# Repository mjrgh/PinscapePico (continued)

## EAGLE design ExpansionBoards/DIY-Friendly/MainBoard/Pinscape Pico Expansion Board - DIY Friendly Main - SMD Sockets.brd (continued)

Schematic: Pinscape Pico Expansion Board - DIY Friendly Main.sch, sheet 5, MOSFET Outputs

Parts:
C1, C3, C5, C7, C11, C13: 100nF; C025-024X044; PARTNO 21RZ310-RC
C2, C4, C6, C8, C12, C14: 4.7uF; C025-024X044; PARTNO 810-FG14X5R1H475KRT0
IC1, IC2, IC3, IC4, IC5, IC6: UCC27524P; DIP794W53P254L959H508Q8N
J3: 640445-5; HDRV5W117P0X396_1X5_1981X762X1
J4: 640445-9; SHDR9W117P0X396_1X9_3566X762X1
Q1, Q2, Q3, Q4, Q5, Q6, Q7, Q8, Q9, Q10, Q11, Q12: FDPF085N10A; TO220BV; PARTNO FDPF085N10A
R1, R2, R3, R4, R5, R6, R7, R8, R14, R15, R16, R17: 4R7; 0204/5; PARTNO 660-MFS1/4DCT52R47R0

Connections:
12V: C1.2, C2.2, C3.2, C4.2, C5.2, C6.2, C7.2, C8.2, C11.2, C12.2, C13.2, C14.2, IC1.1 (ENA), IC1.6 (VDD), IC1.8 (ENB), IC2.1 (ENA), IC2.6 (VDD), IC2.8 (ENB), IC3.1 (ENA), IC3.6 (VDD), IC3.8 (ENB), IC4.1 (ENA), IC4.6 (VDD), IC4.8 (ENB), IC5.1 (ENA), IC5.6 (VDD), IC5.8 (ENB), IC6.1 (ENA), IC6.6 (VDD), IC6.8 (ENB); also elsewhere on the board
unnamed: IC1.7 (OUTA), R1.1
unnamed: IC1.5 (OUTB), R2.1
unnamed: Q1.1 (G), R1.2
unnamed: Q2.1 (G), R2.2
unnamed: IC2.7 (OUTA), R3.1
unnamed: IC2.5 (OUTB), R4.1
unnamed: Q3.1 (G), R3.2
unnamed: Q4.1 (G), R4.2
unnamed: IC3.7 (OUTA), R5.1
unnamed: IC3.5 (OUTB), R6.1
unnamed: Q5.1 (G), R5.2
unnamed: Q6.1 (G), R6.2
unnamed: IC4.7 (OUTA), R7.1
unnamed: IC4.5 (OUTB), R8.1
unnamed: Q7.1 (G), R7.2
unnamed: Q8.1 (G), R8.2
unnamed: IC5.7 (OUTA), R14.1
unnamed: IC5.5 (OUTB), R15.1
unnamed: Q9.1 (G), R14.2
unnamed: Q10.1 (G), R15.2
unnamed: IC6.7 (OUTA), R16.1
unnamed: IC6.5 (OUTB), R17.1
unnamed: Q11.1 (G), R16.2
unnamed: Q12.1 (G), R17.2
OUT1: J4.1, Q1.2 (D)
OUT2: J4.3, Q2.2 (D)
OUT3: J4.4, Q3.2 (D)
OUT4: J4.5, Q4.2 (D)
OUT5: J4.6, Q5.2 (D)
OUT6: J4.7, Q6.2 (D)
OUT7: J4.8, Q7.2 (D)
OUT8: J4.9, Q8.2 (D)
OUT9: J3.1, Q9.2 (D)
OUT10: J3.3, Q10.2 (D)
OUT11: J3.4, Q11.2 (D)
OUT12: J3.5, Q12.2 (D)
OUTCTL1: IC1.2 (INA); also elsewhere on the board
OUTCTL2: IC1.4 (INB); also elsewhere on the board
OUTCTL3: IC2.2 (INA); also elsewhere on the board
OUTCTL4: IC2.4 (INB); also elsewhere on the board
OUTCTL5: IC3.2 (INA); also elsewhere on the board
OUTCTL6: IC3.4 (INB); also elsewhere on the board
OUTCTL7: IC4.2 (INA); also elsewhere on the board
OUTCTL8: IC4.4 (INB); also elsewhere on the board
OUTCTL9: IC5.2 (INA); also elsewhere on the board
OUTCTL10: IC5.4 (INB); also elsewhere on the board
OUTCTL11: IC6.2 (INA); also elsewhere on the board
OUTCTL12: IC6.4 (INB); also elsewhere on the board

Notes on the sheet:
High-power MOSFET drive ports
KEY
High-power MOSFET drivers

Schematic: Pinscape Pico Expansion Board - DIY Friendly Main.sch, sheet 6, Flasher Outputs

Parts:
IC7, IC8, IC9, IC10: ULN2803A; DIL18
J1: 30316-6002HB; 3M-30316-6002HB
J13: 640445-2; SHDR2W117P0X396_1X2_792X762X11

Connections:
5V: J1.2; also elsewhere on the board
FLASHCTL1: IC7.1 (I1), IC7.2 (I2); also elsewhere on the board
FLASHCTL2: IC7.3 (I3), IC7.4 (I4); also elsewhere on the board
FLASHCTL3: IC7.5 (I5), IC7.6 (I6); also elsewhere on the board
FLASHCTL4: IC7.7 (I7), IC7.8 (I8); also elsewhere on the board
FLASHCTL5: IC8.1 (I1), IC8.2 (I2); also elsewhere on the board
FLASHCTL6: IC8.3 (I3), IC8.4 (I4); also elsewhere on the board
FLASHCTL7: IC8.5 (I5), IC8.6 (I6); also elsewhere on the board
FLASHCTL8: IC8.7 (I7), IC8.8 (I8); also elsewhere on the board
FLASHCTL9: IC10.7 (I7), IC10.8 (I8); also elsewhere on the board
FLASHCTL10: IC10.5 (I5), IC10.6 (I6); also elsewhere on the board
FLASHCTL11: IC10.3 (I3), IC10.4 (I4); also elsewhere on the board
FLASHCTL12: IC10.1 (I1), IC10.2 (I2); also elsewhere on the board
FLASHCTL13: IC9.5 (I5), IC9.6 (I6); also elsewhere on the board
FLASHCTL14: IC9.3 (I3), IC9.4 (I4); also elsewhere on the board
FLASHCTL15: IC9.1 (I1), IC9.2 (I2); also elsewhere on the board
FLASHCTL16: IC9.7 (I7), IC9.8 (I8); also elsewhere on the board
FLASHER1: IC7.17 (O2), IC7.18 (O1), J1.15
FLASHER2: IC7.15 (O4), IC7.16 (O3), J1.13
FLASHER3: IC7.13 (O6), IC7.14 (O5), J1.11
FLASHER4: IC7.11 (O8), IC7.12 (O7), J1.9
FLASHER5: IC8.17 (O2), IC8.18 (O1), J1.7
FLASHER6: IC8.15 (O4), IC8.16 (O3), J1.5
FLASHER7: IC8.13 (O6), IC8.14 (O5), J1.3
FLASHER8: IC8.11 (O8), IC8.12 (O7), J1.1
FLASHER9: IC10.11 (O8), IC10.12 (O7), J1.16
FLASHER10: IC10.13 (O6), IC10.14 (O5), J1.14
FLASHER11: IC10.15 (O4), IC10.16 (O3), J1.12
FLASHER12: IC10.17 (O2), IC10.18 (O1), J1.10
FLASHER13: IC9.13 (O6), IC9.14 (O5), J1.8
FLASHER14: IC9.15 (O4), IC9.16 (O3), J1.6
FLASHER15: IC9.17 (O2), IC9.18 (O1), J1.4
FLASHER16: IC9.11 (O8), IC9.12 (O7), J13.1

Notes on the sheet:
RGB Flashers, 1A each port (designed 5x RGB) Pinscape v1 board compatible connector

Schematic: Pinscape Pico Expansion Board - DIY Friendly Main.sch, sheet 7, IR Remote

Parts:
C16: 4.7uF; C025-024X044; PARTNO 810-FG14X5R1H475KRT0
D3, D4: 1N4148; DO35-7
J10: 215079-4; 2150794
J11: 640454-2; HDRV2W66P0X254_1X2_762X572X100
Q13: BC337-25; BC33725
R19: 1.8K; 0204/7; PARTNO 660-MFS1/4DCT52R47R0
R31: 2R5; 0204/7; PARTNO 660-MFS1/4DCT52R47R0

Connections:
3V3_PICO: J10.1; also elsewhere on the board
5V: C16.1, J11.1; also elsewhere on the board
$N377: D3.A, Q13.2 (B), R19.2
IR_IN: J10.3; also elsewhere on the board
IR_LED_CATHODE: J11.2, Q13.1 (C)
IR_OUT: R19.1; also elsewhere on the board
unnamed: D3.C, D4.A
unnamed: Q13.3 (E), R31.2

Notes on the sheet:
IR REMOTE CONTROL TRANSMITTER Use with TSAL6400 IRED or equivalent, with a peak wavelength around 940nm. Set the current-sense resistor according to the desired forward current on the IR LED. The IR LED should be connected directly to the header (no external resistor is needed). Two IR LEDs can be 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
IR REMOTE RECEIVER CONNECTOR This header allows connecting an IR receiver (TSOP38438) on a separate circuit board, connected to the main board with a 4-conductor ribbon cable. The board should include the VCC supply filter circuit (220R + 150nF) shown in the data sheet.
===> IRED Cathode (-)
===> IRED Anode (+)
Note: TE Connectivity Micro-Match 215079-4 base pairs with 215083-4 on-cable IDC connector.
Resistor sets current to I(LED) = 0.5V/R R=2.5 ohms -> 200mA current
NPN substitutes: choose any medium-power NPN with Hfe around 100
IR EMITTER / IR RECEIVER The emitter and receiver are designed to be installed remotely to allow placing them in suitable line-of-sight locations.

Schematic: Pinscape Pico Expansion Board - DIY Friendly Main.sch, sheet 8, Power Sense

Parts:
C15: 100nF; C025-024X044; PARTNO 21RZ310-RC
IC13: SN74HC74NE4; DIP794W53P254L1930H508Q14N
IC14: PC827; DIL08
IC15: S-80833CLY; TO-92_(TO-226)
R18: 240R; 0204/7; PARTNO 660-MFS1/4DCT52R47R0
R20, R22: 10K; 0204/7; PARTNO 660-MFS1/4DCT52R47R0
R21: 360R; 0204/7; PARTNO 660-MFS1/4DCT52R47R0

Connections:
3V3_PICO: IC14.6 (COL); also elsewhere on the board
5V: C15.1, IC13.2 (1D), IC13.4 (1!PRE), IC13.14 (VCC), IC14.8 (COL), IC15.2 (VDD); also elsewhere on the board
unnamed: IC13.3 (1CLK), IC14.7 (EMIT), R20.1
unnamed: IC14.2 (C), R18.2
unnamed: IC13.1 (!1CLR), IC15.1 (OUT)
unnamed: IC14.4 (C), R21.2
unnamed: IC13.5 (1Q), IC14.3 (A)
PSU2_STATUS_SENSE: IC14.5 (EMIT), R22.2; also elsewhere on the board
PSU2_STATUS_SET: IC14.1 (A); also elsewhere on the board

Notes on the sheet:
PSU2 Power Sensing This circuit monitors the status of a secondary power supply (PSU2) that's hard-switched on and off with the overall pinball cabinet power. The status circuit maintains its own memory of the power state, independently of the Pico's power state, which satisfies two important condi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
POR part selection: The POR is triggered by the voltage on the 5V supply crossing a threshold voltage, so we must choose a POR whose threshold voltage slightly below the MINIMUM voltage that the 5V supply maintains when powered on and operating stably. Nominally, this would be 4.75V for an ATX supp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
Note: RESET signal must be ACTIVE LOW

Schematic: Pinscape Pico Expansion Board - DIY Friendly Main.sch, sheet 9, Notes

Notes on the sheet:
I2C Address Map (7-bit notation) $18 LIS3DH (Accelerometer) $30 Pico PWM Helper (main board) $31 Pico PWM Helper #1 (power board) $32 Pico PWM Helper #2 (power board) $48 ADS1115 (ADC) $68 DS1307 (RTC clock/calendar chip) [On Power board]

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
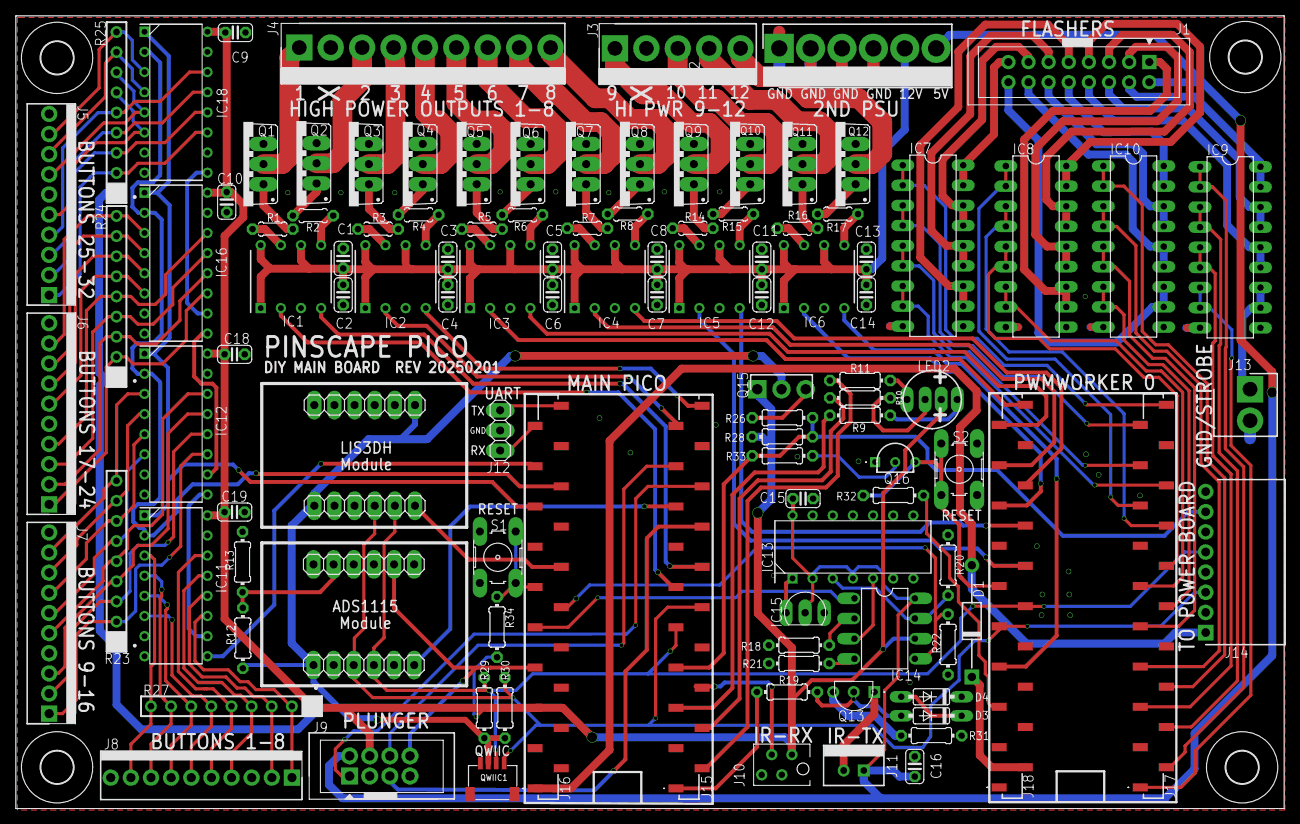
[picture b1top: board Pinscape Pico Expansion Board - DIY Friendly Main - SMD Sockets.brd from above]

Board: 2 copper layers, 160.0 x 100.0 mm, 117 parts (0 on the bottom side), 161 nets.

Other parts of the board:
J15, J16, J17, J18: M20-7862042B; M20-7862042-B
U$1, U$2, U$3, U$4: 4,1

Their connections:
3V3_PICO: J16.5; also elsewhere on the board
ACCEL_INTR: J16.12; also elsewhere on the board
ADC_INTR: J15.15; also elsewhere on the board
BUTTON_CLK: J16.16; also elsewhere on the board
BUTTON_DATA: J16.17; also elsewhere on the board
BUTTON_SHLD: J16.15; also elsewhere on the board
FLASHCTL1: J17.20; also elsewhere on the board
FLASHCTL2: J17.19; also elsewhere on the board
FLASHCTL3: J17.17; also elsewhere on the board
FLASHCTL4: J17.16; also elsewhere on the board
FLASHCTL5: J17.15; also elsewhere on the board
FLASHCTL6: J17.14; also elsewhere on the board
FLASHCTL7: J17.12; also elsewhere on the board
FLASHCTL8: J17.11; also elsewhere on the board
FLASHCTL9: J17.10; also elsewhere on the board
FLASHCTL10: J17.9; also elsewhere on the board
FLASHCTL11: J17.7; also elsewhere on the board
FLASHCTL12: J17.6; also elsewhere on the board
FLASHCTL13: J17.5; also elsewhere on the board
FLASHCTL14: J17.4; also elsewhere on the board
FLASHCTL15: J17.2; also elsewhere on the board
FLASHCTL16: J17.1; also elsewhere on the board
IR_IN: J15.6; also elsewhere on the board
IR_OUT: J15.1; also elsewhere on the board
LED_B: J15.4; also elsewhere on the board
LED_G: J15.2; also elsewhere on the board
LED_R: J15.5; also elsewhere on the board
unnamed 103: J18.2; also elsewhere on the board
unnamed 120: J18.5; also elsewhere on the board
OUTCTL1: J15.11; also elsewhere on the board
OUTCTL2: J15.12; also elsewhere on the board
OUTCTL3: J15.19; also elsewhere on the board
OUTCTL4: J15.20; also elsewhere on the board
OUTCTL5: J18.20; also elsewhere on the board
OUTCTL6: J18.19; also elsewhere on the board
OUTCTL7: J18.17; also elsewhere on the board
OUTCTL8: J18.16; also elsewhere on the board
OUTCTL9: J18.12; also elsewhere on the board
OUTCTL10: J18.14; also elsewhere on the board
OUTCTL11: J18.15; also elsewhere on the board
OUTCTL12: J18.7; also elsewhere on the board
PLUNGER_ADC: J16.7; also elsewhere on the board
PLUNGER_IRQ1_SCL: J15.17; also elsewhere on the board
PLUNGER_IRQ2: J15.14; also elsewhere on the board
PLUNGER_SDA: J15.16; also elsewhere on the board
PSU2_STATUS_SENSE: J16.10; also elsewhere on the board
PSU2_STATUS_SET: J16.9; also elsewhere on the board
UART0_RX: J16.19; also elsewhere on the board
UART0_TX: J16.20; also elsewhere on the board

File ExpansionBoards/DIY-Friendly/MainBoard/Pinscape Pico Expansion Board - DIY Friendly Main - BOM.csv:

Qty,Value,Parts,Description,PARTNO,Comments
2,B3F-1000,"S1, S2","Omron pushbutton switch, SPST, through-hole",B3F-1000,
4,"0.1"" SOCK-HD 1X6","JP1, JP2, JP3, JP4","Pin Socket Header, 1x6",61300611821,
1,"0.1"" PIN-HD 1X3",J12,"Pin Header, 1x3",2PH1-03-UA,
4,"0.1"" SOCK-HD 1X20","PICO1, PICO2","Socket Header, 20 position, 2.54mm pitch",61302011821,
2,Pico-H,"PICO1, PICO2",Raspberry Pi Pico w/pin headers installed,SC0917,
4,MTA100-10PIN,"J5, J6, J7, J8",10 way MTA100 straight friction lock header,1-640456-0,
4,MTA100-10PIN-24AWG,"PLUG_J5, PLUG_J6, PLUG_J7, PLUG_J8","Plug for J5 J6 J7 J8, 10p IDC housing 24 AWG",4-644563-0,
1,100R,R9,"Resistor, 100 Ohm, axial, 2mm 4 xmm",MFR-12FTE52-100R,
11,100nF,"C1, C3, C5, C7, C9, C10, C11, C13, C15, C18, C19","Capacitor, ceramic, 100nF, radial, 2.5mm lead pitch",K104K15X7RF5TL2,
4,10K,"R12, R13, R20, R22","Resistor, 10K, axial, 2mm x 4mm",MFR-12FRF52-10K,
2,10R,"R10, R11","Resistor, 10 Ohm, axial, 2mm 4 xmm",MFR25SFTE52-10R,
2,15K,"R29, R30","Resistor, 15K, axial, 2mm x 4mm",MFR25SFRF52-15K,
1,1K,R26,"Resistor, 1K, axial, 2mm x 4mm",MF0204FTE52-1K,
2,1N4148,"D3, D4","Diode, 1N4148, axial",1N4148-T50A,
1,2.2k,R33,"Resistor, 2.2K, axial, 2mm x 4mm",MF0204FTE52-2K2,
1,MICROMATCH-4PIN,J10,"Connector, Micro-MaTch female-on-board, 4 pin, top entry",215079-4,
1,MICROMATCH-4PIN,PLUG_J10,"Plug for J10, Micro-MaTch male-on-wire, 4 pin, IDC",215083-4,
1,22K,R28,"Resistor, 22K, axial, 2mm 4 xmm",MFR-12FTF52-22K,
1,240R,R18,"Resistor, 240 Ohm, axial, 2mm 4 4mm",MFR25SFTF52-240R,
1,2N2222A,Q16,"NPN transistor, 2N2222A, TO-92, 40V, 600mA",637-2N2222A,
1,2N5195G,Q15,"PNP transistor, 2N5195G, TO-225-3, 80V, 4A",2N5195G,
1,2R5,R31,"Resistor, 2.5 Ohm, 1%, axial, 2mm x 4mm",MFR-25FTE52-2R49,
1,"0.1"" PIN-HD 2X4",J9,"Shrouded pin header 0.1"" 2x4",737-BHR-16-VUA,
1,"0.1"" IDC 2X4",PLUG_J9,"IDC housing, 0.1"", 2x4",737-FCS-16-SG,
1,"0.1"" PIN-HD 2X8",J1,"Shrouded pin header 0.1"" 2x8",737-BHR-16-VUA,
1,"0.1"" IDC 2X8",PLUG_J9,"IDC housing, 0.1"", 2x8",737-FCS-08-SG,
1,360R,R21,"Resistor, 360 Ohm, axial, 2mm x 4mm",MFR-12FTF52-360R,
2,4.7K,"R32, R34","Resistor, 4.7K, axial, 2mm x 4mm",MFR25SFRF52-4K7,
7,4.7uF,"C2, C4, C6, C8, C12, C14, C16","Capacitor, ceramic, 4.7uF, radial, 2.5mm lead pitch",FG14X7R1E475KRT06,
4,10K X 8,"R23, R24, R25, R27","Resistor network, bussed, 10K, 9 pin, through-hole 0.1"" pitch",4609X-101-103LF,
12,4R7,"R1, R2, R3, R4, R5, R6, R7, R8, R14, R15, R16, R17","Resistor, 4.7 Ohm, axial, 2 mm x 4mm",MF0204FTE52-4R7,"Gate driver resistor; current limit 2.5A, fastest switching"
12,47R,"R1, R2, R3, R4, R5, R6, R7, R8, R14, R15, R16, R17","Resistor, 47 Ohm, axial, 2 mm x 4mm",MFR25SFRF52-47R,Alternate gate driver resistor; current limit 255mA - see notes
12,200R,"R1, R2, R3, R4, R5, R6, R7, R8, R14, R15, R16, R17","Resistor, 200 Ohm, axial, 2 mm x 4mm",MFR25SFRF52-200R,Alternate gate driver resistor; current limit 60mA - see notes
1,RGB-LED-CA,LED2,"RGB LED, Through Hole 5mm, 4 leads, common anode",521-8559F,
1,540R,R19,"Resistor, 540 Ohm, axial, 2 mm x 4mm",CFR-12JT-52-540R,
1,MTA156-2PIN,J13,"MTA156 friction lock header, 3.96mm pitch, 2 position",640445-2,
1,MTA156-2PIN-22AWG,PLUG_J13,"MTA156 IDC housing, 2 pin, 22 AWG",3-643819-2,
1,MTA156-5PIN,J3,"MTA156 friction lock header, 3.96mm pitch, 5 position",640445-5,
1,MTA156-5PIN-22AWG,PLUG_J3,"MTA156 IDC housing, 5 pin, 22 AWG",3-643819-5,
1,MTA156-6PIN,J2,"MTA156 friction lock header, 3.96mm pitch, 6 position",640445-6,
1,MTA156-6PIN-22AWG,PLUG_J2,"MTA156 IDC housing, 6 pin, 22 AWG",3-643819-6,
1,MTA156-9PIN,J4,"MTA156 friction lock header, 3.96mm pitch, 9 position",640445-9,
1,MTA156-9PIN-22AWG,PLUG_J4,"MTA156 IDC housing, 9 pin, 22 AWG",3-640428-9,
1,MTA100-2PIN,J11,"MTA100 friction lock header, 2.54mm pitch, 2 position",640454-2,
1,MTA100-2PIN-24AWG,PLUG_J11,"MTA100 housing, 2 pin, 24 AWG",3-643814-2,
1,BC337-25,Q13,"NPN transistor, BC337-25, TO-92, 45V, 800mA",637-BC337-25,
12,FDPF085N10A,"Q1, Q2, Q3, Q4, Q5, Q6, Q7, Q8, Q9, Q10, Q11, Q12","Power MOSFET, TO-220-3 (G-D-S pin ordering)",FDPF085N10A,Substitute any N-channel TO-220-3 with G-D-S pin ordering and minimum 20V V[gs][max]
1,PC827,IC14,Sharp 2-channel optocoupler LTV-827,LTV-827,
1,JST-SR/SZ-4PIN,QWIIC1,"JST SR/SZ 4-position side entry header, SMD",SM04B-SRSS-TB(LF)(SN),
1,S-80834CLY-B2-U,IC15,"Voltage detector, TO-92-3, active low CMOS out, 3.4V",S-80834CLY-B2-U,Substitute any S-808xxCLY-x2-U with 3.0 to 4.0 threshold voltage ('xx' in product code)
1,SB140-T,D1,"Schottky Diodes & Rectifiers 1.0A 40V, SB140-T, through-hole",SB140-T,
4,SN74HC165N,"IC11, IC12, IC16, IC18","SN74HC165N 8-bit input shift register, through-hole",SN74HC165N,
1,SN74HC74NE4,IC13,"SN74HC74NE4 dual flip-flop, through-hole",SN74HC74NE4,
1,"0.1"" SOCK-HD 1X8",J14,"Socket header, 8 position, 0.1"" pitch, right-angle",SSQ-108-02-T-S-RA,
6,UCC27524P,"IC1, IC2, IC3, IC4, IC5, IC6",Dual 5A High-Speed Low-Side Power MOSFET Driver,UCC27524P,
4,ULN2803A,"IC7, IC8, IC9, IC10","Darlington NPN transistor array, 500mA/ch",ULN2803A,
1,ADS1115,,Adafruit ADS1115 STEMMA module,485-1085,
1,LIS3DH,,Adafruit LIS3DH STEMMA module,485-2809,
1,TSAL6400,,"Vishay IR emitter, 940nm, T-1.75, TSAL6400",TSAL6400,"IR emitter LED, connects to J11 for off-board placement"
1,VSLB4940,,"Vishay IR emitter, 940nm, T-1, VSLB4940",VSLB4940,"Alternate IR emitter LED, connects to J11 for off-board placement"

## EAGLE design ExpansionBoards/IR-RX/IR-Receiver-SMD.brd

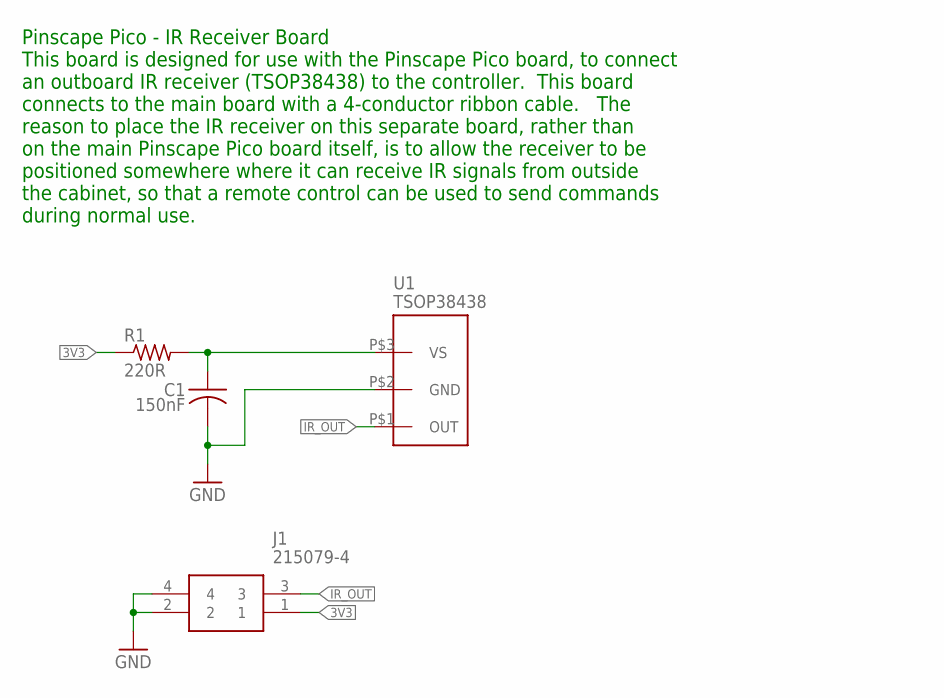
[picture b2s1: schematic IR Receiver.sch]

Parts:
C1: 150nF; C1206
J1: 215079-4; 2150794
R1: 220R; R1206; PARTNO 660-MS1/4DCT52R1002
U1: TSOP38438; TSOP382

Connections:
3V3: J1.1, R1.1
GND: C1.2, J1.2, J1.4, U1.P$2 (GND)
IR_OUT: J1.3, U1.P$1 (OUT)
unnamed: C1.1, R1.2, U1.P$3 (VS)

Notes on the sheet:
Pinscape Pico - IR Receiver Board This board is designed for use with the Pinscape Pico board, to connect an outboard IR receiver (TSOP38438) to the controller. This board connects to the main board with a 4-conductor ribbon cable. The reason to place the IR receiver on this separate board, rather 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

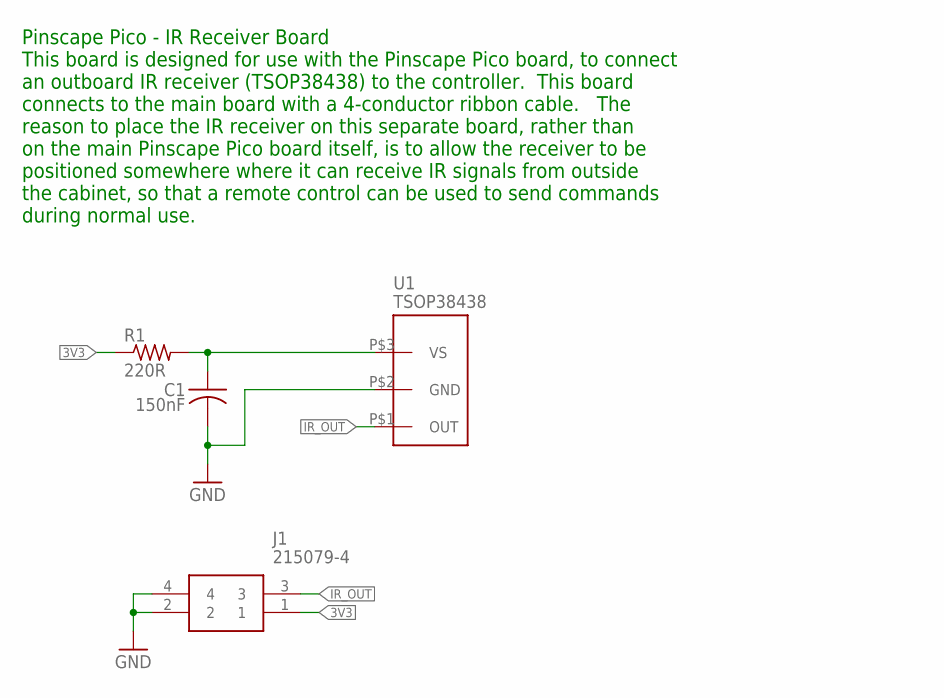
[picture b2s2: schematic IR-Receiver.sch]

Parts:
C1: 150nF; C025-040X050
J1: 215079-4; 2150794
R1: 220R; 0204/7; PARTNO 660-MS1/4DCT52R1002
U1: TSOP38438; TSOP382

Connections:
3V3: J1.1, R1.1
GND: C1.2, J1.2, J1.4, U1.P$2 (GND)
IR_OUT: J1.3, U1.P$1 (OUT)
unnamed: C1.1, R1.2, U1.P$3 (VS)

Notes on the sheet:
Pinscape Pico - IR Receiver Board This board is designed for use with the Pinscape Pico board, to connect an outboard IR receiver (TSOP38438) to the controller. This board connects to the main board with a 4-conductor ribbon cable. The reason to place the IR receiver on this separate board, rather 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

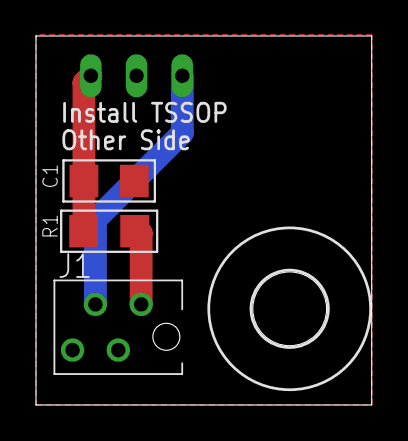
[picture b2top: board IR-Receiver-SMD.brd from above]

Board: 2 copper layers, 18.6 x 20.5 mm, 5 parts (1 on the bottom side), 4 nets.

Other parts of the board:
U$3: 4,1

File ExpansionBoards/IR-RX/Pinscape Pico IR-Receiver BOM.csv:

Qty,Value,Parts,Description,PARTNO,Comments
1,150nF,C1,"Capacitor, ceramic, 150nF, radial, 2.5mm lead pitch",K154K20X7RF53H5,
1,220R,R1,"Resistor, 200 Ohm, axial, 2mm 4 xmm",MFR25SFTF52-220R,
1,TSOP38438,U1,"IR receiver/demodulator, Vishay TSOP38438",TSOP38438,
1,MICROMATCH-4PIN,J1,"Connector, Micro-MaTch female-on-board, 4 pin, top entry",215079-4,
1,MICROMATCH-4PIN,PLUG_J1,"Plug for J1, Micro-MaTch male-on-wire, 4 pin, IDC",215083-4,

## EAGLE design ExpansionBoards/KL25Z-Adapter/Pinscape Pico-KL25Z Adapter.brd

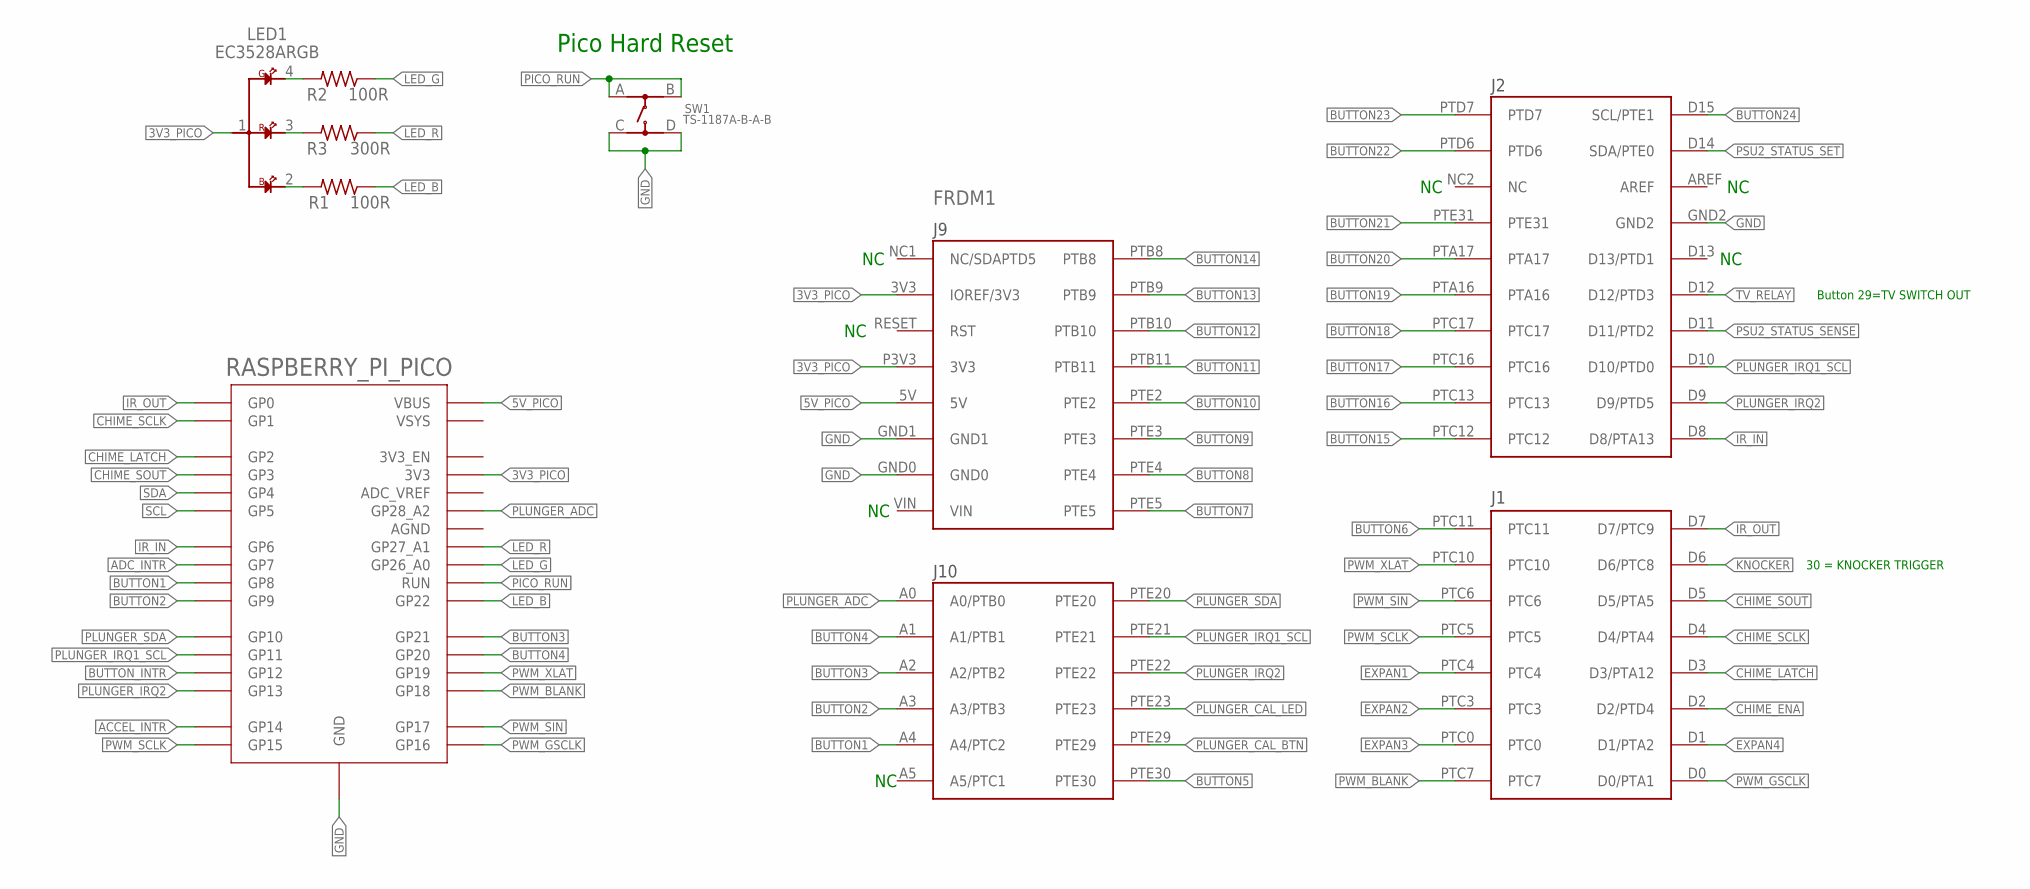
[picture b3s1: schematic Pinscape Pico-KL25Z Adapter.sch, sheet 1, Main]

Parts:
FRDM1: KL25Z; FRDM_KL25Z_NORMAL
LED1: EC3528ARGB
R1, R2: 100R; R1206
R3: 300R; R1206
RASPBERRY_PI_PICO: RPI_PICO_NO_DEBUG; RPI_PICO_TH_NO_DEBUG
SW1: TS-1187A-B-A-B

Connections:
3V3_PICO: FRDM1.3V3 (IOREF/3V3), FRDM1.P3V3 (3V3), LED1.1, RASPBERRY_PI_PICO.3V3; also elsewhere on the board
5V_PICO: FRDM1.5V, RASPBERRY_PI_PICO.VBUS
ACCEL_INTR: RASPBERRY_PI_PICO.GP14; also elsewhere on the board
ADC_INTR: RASPBERRY_PI_PICO.GP7; also elsewhere on the board
BUTTON1: FRDM1.A4 (A4/PTC2), RASPBERRY_PI_PICO.GP8
BUTTON2: FRDM1.A3 (A3/PTB3), RASPBERRY_PI_PICO.GP9
BUTTON3: FRDM1.A2 (A2/PTB2), RASPBERRY_PI_PICO.GP21
BUTTON4: FRDM1.A1 (A1/PTB1), RASPBERRY_PI_PICO.GP20
BUTTON5: FRDM1.PTE30; also elsewhere on the board
BUTTON6: FRDM1.PTC11; also elsewhere on the board
BUTTON7: FRDM1.PTE5; also elsewhere on the board
BUTTON8: FRDM1.PTE4; also elsewhere on the board
BUTTON9: FRDM1.PTE3; also elsewhere on the board
BUTTON10: FRDM1.PTE2; also elsewhere on the board
BUTTON11: FRDM1.PTB11; also elsewhere on the board
BUTTON12: FRDM1.PTB10; also elsewhere on the board
BUTTON13: FRDM1.PTB9; also elsewhere on the board
BUTTON14: FRDM1.PTB8; also elsewhere on the board
BUTTON15: FRDM1.PTC12; also elsewhere on the board
BUTTON16: FRDM1.PTC13; also elsewhere on the board
BUTTON17: FRDM1.PTC16; also elsewhere on the board
BUTTON18: FRDM1.PTC17; also elsewhere on the board
BUTTON19: FRDM1.PTA16; also elsewhere on the board
BUTTON20: FRDM1.PTA17; also elsewhere on the board
BUTTON21: FRDM1.PTE31; also elsewhere on the board
BUTTON22: FRDM1.PTD6; also elsewhere on the board
BUTTON23: FRDM1.PTD7; also elsewhere on the board
BUTTON24: FRDM1.D15 (SCL/PTE1); also elsewhere on the board
BUTTON_INTR: RASPBERRY_PI_PICO.GP12; also elsewhere on the board
CHIME_ENA: FRDM1.D2 (D2/PTD4); also elsewhere on the board
CHIME_LATCH: FRDM1.D3 (D3/PTA12), RASPBERRY_PI_PICO.GP2
CHIME_SCLK: FRDM1.D4 (D4/PTA4), RASPBERRY_PI_PICO.GP1
CHIME_SOUT: FRDM1.D5 (D5/PTA5), RASPBERRY_PI_PICO.GP3
EXPAN1: FRDM1.PTC4; also elsewhere on the board
EXPAN2: FRDM1.PTC3; also elsewhere on the board
EXPAN3: FRDM1.PTC0; also elsewhere on the board
EXPAN4: FRDM1.D1 (D1/PTA2); also elsewhere on the board
GND: FRDM1.GND0, FRDM1.GND1, FRDM1.GND2, RASPBERRY_PI_PICO.GND@1 (GND), RASPBERRY_PI_PICO.GND@2 (GND), RASPBERRY_PI_PICO.GND@3 (GND), RASPBERRY_PI_PICO.GND@4 (GND), RASPBERRY_PI_PICO.GND@6 (GND), RASPBERRY_PI_PICO.GND@7 (GND), RASPBERRY_PI_PICO.GND@8 (GND), SW1.C, SW1.D; also elsewhere on the board
IR_IN: FRDM1.D8 (D8/PTA13), RASPBERRY_PI_PICO.GP6
IR_OUT: FRDM1.D7 (D7/PTC9), RASPBERRY_PI_PICO.GP0
KNOCKER: FRDM1.D6 (D6/PTC8); also elsewhere on the board
LED_B: R1.1, RASPBERRY_PI_PICO.GP22
LED_G: R2.1, RASPBERRY_PI_PICO.GP26_A0
LED_R: R3.1, RASPBERRY_PI_PICO.GP27_A1
unnamed: LED1.3, R3.2
unnamed: LED1.2, R1.2
unnamed: LED1.4, R2.2
PICO_RUN: RASPBERRY_PI_PICO.RUN, SW1.A, SW1.B
PLUNGER_ADC: FRDM1.A0 (A0/PTB0), RASPBERRY_PI_PICO.GP28_A2; also elsewhere on the board
PLUNGER_CAL_BTN: FRDM1.PTE29; also elsewhere on the board
PLUNGER_CAL_LED: FRDM1.PTE23; also elsewhere on the board
PLUNGER_IRQ1_SCL: FRDM1.D10 (D10/PTD0), FRDM1.PTE21, RASPBERRY_PI_PICO.GP11
PLUNGER_IRQ2: FRDM1.D9 (D9/PTD5), FRDM1.PTE22, RASPBERRY_PI_PICO.GP13
PLUNGER_SDA: FRDM1.PTE20, RASPBERRY_PI_PICO.GP10
PSU2_STATUS_SENSE: FRDM1.D11 (D11/PTD2); also elsewhere on the board
PSU2_STATUS_SET: FRDM1.D14 (SDA/PTE0); also elsewhere on the board
PWM_BLANK: FRDM1.PTC7, RASPBERRY_PI_PICO.GP18
PWM_GSCLK: FRDM1.D0 (D0/PTA1), RASPBERRY_PI_PICO.GP16
PWM_SCLK: FRDM1.PTC5, RASPBERRY_PI_PICO.GP15
PWM_SIN: FRDM1.PTC6, RASPBERRY_PI_PICO.GP17
PWM_XLAT: FRDM1.PTC10, RASPBERRY_PI_PICO.GP19
SCL: RASPBERRY_PI_PICO.GP5; also elsewhere on the board
SDA: RASPBERRY_PI_PICO.GP4; also elsewhere on the board
TV_RELAY: FRDM1.D12 (D12/PTD3); also elsewhere on the board

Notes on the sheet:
Button 29=TV SWITCH OUT
30 = KNOCKER TRIGGER
Pico Hard Reset

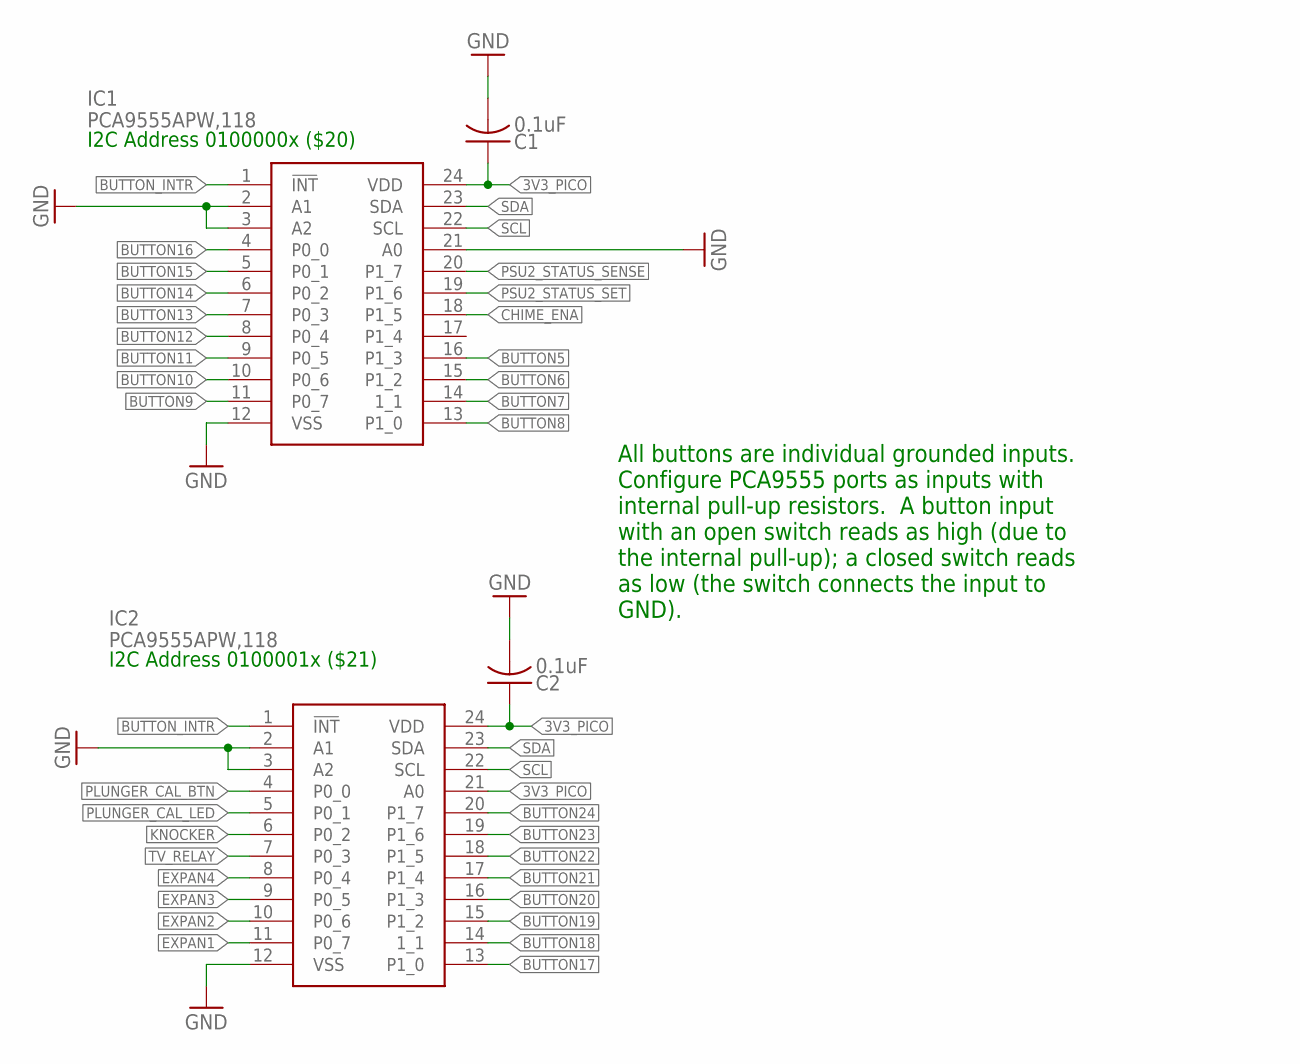
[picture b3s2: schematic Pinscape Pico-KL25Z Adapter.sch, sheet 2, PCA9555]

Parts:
C1, C2: 0.1uF; C1206
IC1, IC2: PCA9555APW,118; SOP65P640X110-24N

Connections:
3V3_PICO: C1.1, C2.1, IC1.24 (VDD), IC2.21 (A0), IC2.24 (VDD); also elsewhere on the board
BUTTON5: IC1.16 (P1_3); also elsewhere on the board
BUTTON6: IC1.15 (P1_2); also elsewhere on the board
BUTTON7: IC1.14 (1_1); also elsewhere on the board
BUTTON8: IC1.13 (P1_0); also elsewhere on the board
BUTTON9: IC1.11 (P0_7); also elsewhere on the board
BUTTON10: IC1.10 (P0_6); also elsewhere on the board
BUTTON11: IC1.9 (P0_5); also elsewhere on the board
BUTTON12: IC1.8 (P0_4); also elsewhere on the board
BUTTON13: IC1.7 (P0_3); also elsewhere on the board
BUTTON14: IC1.6 (P0_2); also elsewhere on the board
BUTTON15: IC1.5 (P0_1); also elsewhere on the board
BUTTON16: IC1.4 (P0_0); also elsewhere on the board
BUTTON17: IC2.13 (P1_0); also elsewhere on the board
BUTTON18: IC2.14 (1_1); also elsewhere on the board
BUTTON19: IC2.15 (P1_2); also elsewhere on the board
BUTTON20: IC2.16 (P1_3); also elsewhere on the board
BUTTON21: IC2.17 (P1_4); also elsewhere on the board
BUTTON22: IC2.18 (P1_5); also elsewhere on the board
BUTTON23: IC2.19 (P1_6); also elsewhere on the board
BUTTON24: IC2.20 (P1_7); also elsewhere on the board
BUTTON_INTR: IC1.1 (!INT), IC2.1 (!INT); also elsewhere on the board
CHIME_ENA: IC1.18 (P1_5); also elsewhere on the board
EXPAN1: IC2.11 (P0_7); also elsewhere on the board
EXPAN2: IC2.10 (P0_6); also elsewhere on the board
EXPAN3: IC2.9 (P0_5); also elsewhere on the board
EXPAN4: IC2.8 (P0_4); also elsewhere on the board
GND: C1.2, C2.2, IC1.2 (A1), IC1.3 (A2), IC1.12 (VSS), IC1.21 (A0), IC2.2 (A1), IC2.3 (A2), IC2.12 (VSS); also elsewhere on the board
KNOCKER: IC2.6 (P0_2); also elsewhere on the board
PLUNGER_CAL_BTN: IC2.4 (P0_0); also elsewhere on the board
PLUNGER_CAL_LED: IC2.5 (P0_1); also elsewhere on the board
PSU2_STATUS_SENSE: IC1.20 (P1_7); also elsewhere on the board
PSU2_STATUS_SET: IC1.19 (P1_6); also elsewhere on the board
SCL: IC1.22 (SCL), IC2.22 (SCL); also elsewhere on the board
SDA: IC1.23 (SDA), IC2.23 (SDA); also elsewhere on the board
TV_RELAY: IC2.7 (P0_3); also elsewhere on the board

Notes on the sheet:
I2C Address 0100000x ($20)
I2C Address 0100001x ($21)
All buttons are individual grounded inputs. Configure PCA9555 ports as inputs with internal pull-up resistors. A button input with an open switch reads as high (due to the internal pull-up); a closed switch reads as low (the switch connects the input to GND).

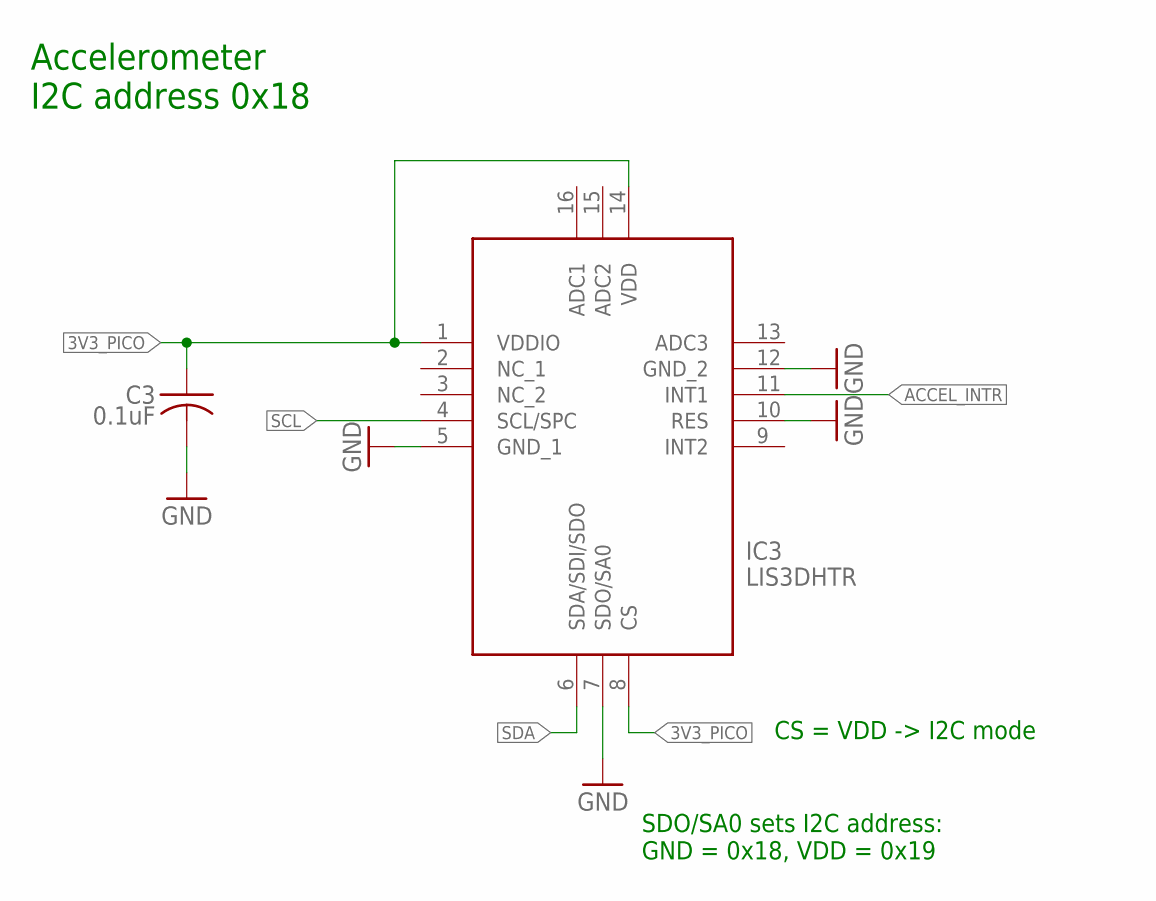
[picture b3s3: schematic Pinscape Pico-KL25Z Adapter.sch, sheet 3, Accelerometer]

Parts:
C3: 0.1uF; C1206
IC3: LIS3DHTR

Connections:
3V3_PICO: C3.1, IC3.1 (VDDIO), IC3.8 (CS), IC3.14 (VDD); also elsewhere on the board
ACCEL_INTR: IC3.11 (INT1); also elsewhere on the board
GND: C3.2, IC3.5 (GND_1), IC3.7 (SDO/SA0), IC3.10 (RES), IC3.12 (GND_2); also elsewhere on the board
SCL: IC3.4 (SCL/SPC); also elsewhere on the board
SDA: IC3.6 (SDA/SDI/SDO); also elsewhere on the board

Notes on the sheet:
Accelerometer I2C address 0x18
SDO/SA0 sets I2C address: GND = 0x18, VDD = 0x19
CS = VDD -> I2C mode

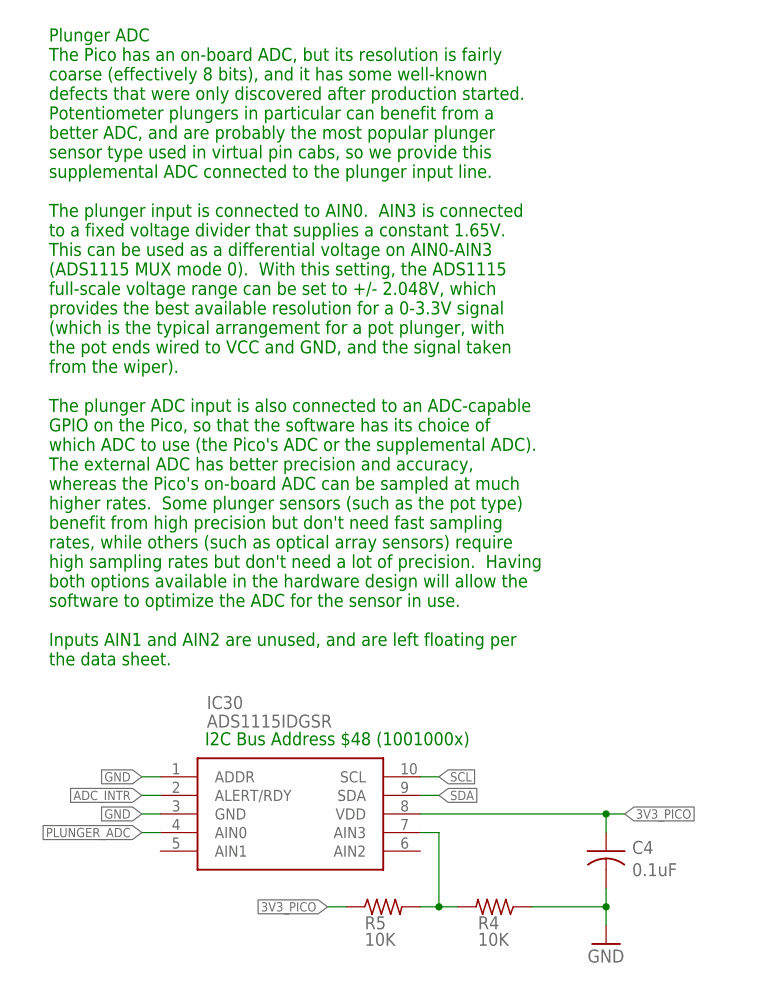
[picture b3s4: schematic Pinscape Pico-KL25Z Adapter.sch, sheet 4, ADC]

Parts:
C4: 0.1uF; C1206
IC30: ADS1115IDGSR; SOP50P490X110-10N
R4, R5: 10K; R1206

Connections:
3V3_PICO: C4.1, IC30.8 (VDD), R5.1; also elsewhere on the board
ADC_INTR: IC30.2 (ALERT/RDY); also elsewhere on the board
GND: C4.2, IC30.1 (ADDR), IC30.3 (GND), R4.1; also elsewhere on the board
unnamed: IC30.7 (AIN3), R4.2, R5.2
PLUNGER_ADC: IC30.4 (AIN0); also elsewhere on the board
SCL: IC30.10 (SCL); also elsewhere on the board
SDA: IC30.9 (SDA); also elsewhere on the board

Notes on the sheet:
I2C Bus Address $48 (1001000x)
Plunger ADC The Pico has an on-board ADC, but its resolution is fairly coarse (effectively 8 bits), and it has some well-known defects that were only discovered after production started. Potentiometer plungers in particular can benefit from a better ADC, and are probably the most popular plunger se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
